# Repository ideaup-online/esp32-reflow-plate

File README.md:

# Solder Reflow Plate Prototype

This is an ESP32 project for controlling a PCB-based solder reflow plate. The solder reflow plate used in this prototype was made using gerbers from [AfterEarthLTD's solder reflow plate](https://github.com/AfterEarthLTD/Solder-Reflow-Plate).

This project was created out of the need to assemble boards using solder reflow. I have some project ideas involving parts that have footprints that can't be soldered any other way.

I became aware of AfterEarthLTD's design after it was featured in a Great Scott! video on YouTube.

At the time I started this, ATmega328 chips are still not available and the code for the ATmega 4809 revision was not yet completed. So, I decided to send the gerbers for the ATmega 4809 revision to JLCPCB to be manufactured.

## Connecting the Solder Reflow Plate to Breadboard Prototype

The boards were populated with only the mosfet (with associated capacitor and zener diode) and the temp sensor (with associated capacitor). I also simply used a 1nF capacitor for both to reduce the number of parts I needed to purchase.

After that, an XT60 connector was soldered with pigtails to the pads for the barrel connector (I did not use the barrel connector). Leads were soldered for the positive side of the XT60, ground, 5V, the gate of the mosfet, and the output of the temp sensor. The positive side of the XT60 was picked up from the pad for the big capacitor that goes next to the barrel connector. Ground and 5V were picked up from the OLED connector through holes. The lead for the gate of the mosfet was soldered directly to the gate pin/pad of the mosfet (mosfet is installed on board). The temp sensor output was picked up from the ATmega 4809 footprint. The leads were terminated in a dupont connector for ease of breadboarding.

I powered all this from the XT60 using battery power of ~13.5V. That voltage was brought over to a breadboard where the rest of the components and the ESP32 were connected. 3.3V from the ESP32 is sent to the board via the 5V lead. This is fine because the only thing I populated that uses the 5V is the temp sensor and it is just as happy with 3.3V. The ground of the board is connected to the ground of the breadboard components. Finally, the gate and temp sensor voltage are passed to the breadboard via their leads.

The battery voltage is brought down to 5V with an XL4015 buck converter to power the ESP32 dev kit board. The ESP32 dev kit then provides 3.3V to everything else.

## Modifications to AfterEarthLTD's Design

Aside from the obvious of using an ESP32 instead of an ATmega, a couple of changes have been made.

The mosfet would not be turned on all the way by simply connecting the gate to one of the ESP32 GPIOs. The max output of 3.3V would not be sufficient. Therefore a DGD0215 gate driver has been used to drive the mosfet.

Also, the ESP32 ADC is not very linear. So, I opted to use a MAX11645 12-bit ADC and MCP1501-20 voltage reference. The LMT85 temp sensor tops out at around 1.9V on its output, so I chose the MCP1501-20 2.048V reference based on that.

Finally, an LED has been added to show when the heater is on (D1).

## 3D Printed Base

A simple 3D printed base has been created. This keeps the board from burning my desk when it gets hot. The STL file for it is here. It needs 4x M3x12 screws, 2x M3 washers, and 4x M3 nuts to assemble. I printed it in PETG on a Prusa Mini.

## Code

The code is not yet complete. The goal is to have the ability to have the board follow a solder reflow profile reasonably closely while being controlled and monitored via a web app running on the ESP32.

For now, there is a 128x64 OLED display just to monitor temperatures. It displays the value from the LMT85 as well as two K-type thermocouples attached via Adafruit MAX31855 breakout boards.

The current version of the code ensures that everything powers up without the heater coming on. The on-board button for GPIO0 can be used to turn on the heater (heater is only on while the button is pressed).

This readme will be updated as the code evolves.

## Should You Build One?

As of now, I would say no. My goal is to spin a new board based on the changes outlined above. I'd also like to try to make the working surface a bit larger than the current 50x70mm.

All that is going to take a little exploring and experimenting. That said, if you would like to do such exploration on your own, then by all means build this as is!

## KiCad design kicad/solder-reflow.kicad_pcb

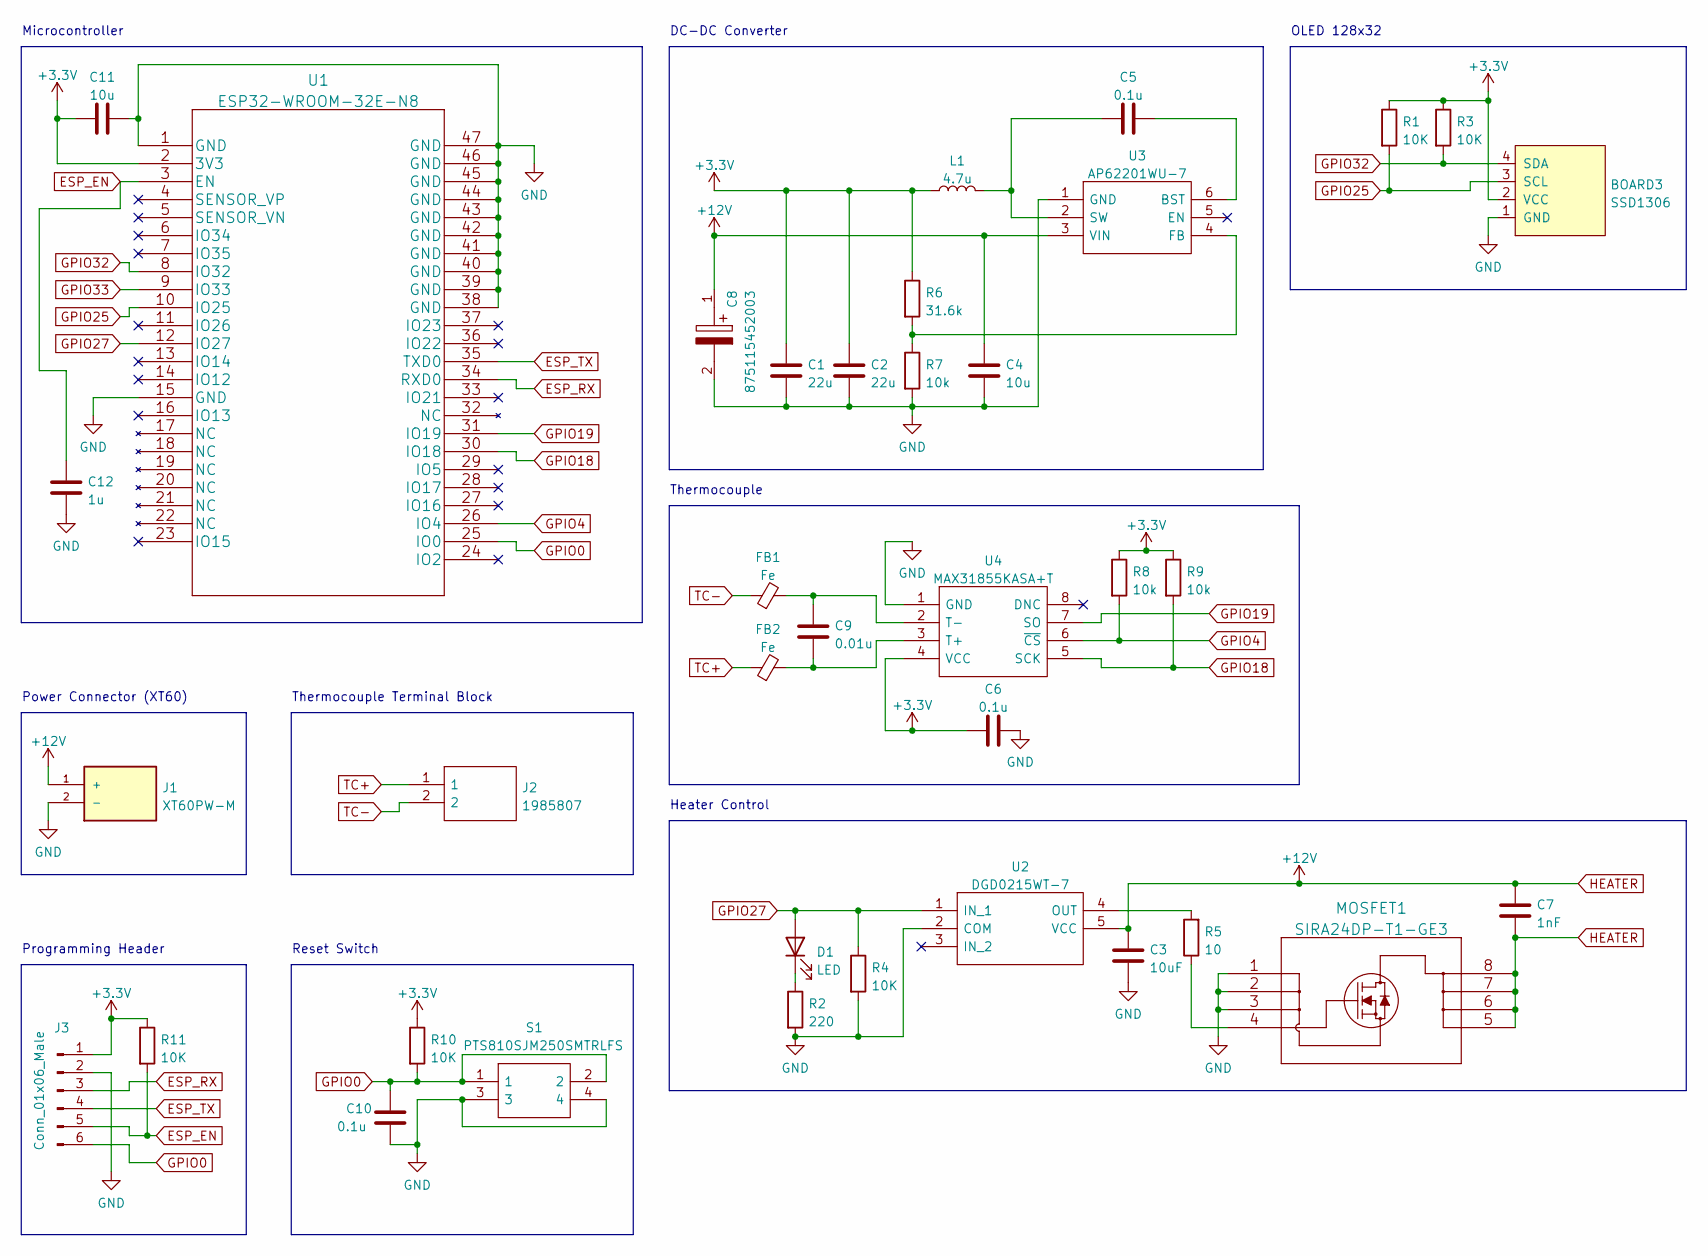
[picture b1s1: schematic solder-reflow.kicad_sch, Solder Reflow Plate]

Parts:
BOARD3: SSD1306; SSD1306-0.91-OLED-4pin-128x32
C1, C2: 22u; 0805
C3: 10uF; 0603
C4: 10u; 0805
C5, C6, C10: 0.1u; 0603
C7: 1nF; 0603
C8: 875115452003; CAPAE830X870N; Mouser Part Number 710-875115452003
C9: 0.01u; 0603
C11: 10u; 0603
C12: 1u; 0603
D1: LED; LED_0603
FB1, FB2: Fe; 0603
J1: XT60PW-M; AMASS_XT60PW-M; PARTREV V1.2
J2: 1985807; Mouser Part Number 651-1985807
J3: Conn_01x06_Male; PinHeader_1x06_P2.54mm_Vertical
L1: 4.7u; IND_NR6028T4R7M
MOSFET1: SIRA24DP-T1-GE3
R1, R3, R4, R10, R11: 10K; 0603
R2: 220; 0603
R5: 10; 0603
R6: 31.6k; 0603
R7, R8, R9: 10k; 0603
S1: PTS810SJM250SMTRLFS; PTS810SJG250SMTRLFS; Mouser Part Number 611-PTS810SJM250SMTR
U1: ESP32-WROOM-32E-N8
U2: DGD0215WT-7; SOT95P280X110-5N; Mouser Part Number 621-DGD0215WT-7
U3: AP62201WU-7; SOT95P280X100-6N; Mouser Part Number 621-AP62201WU-7
U4: MAX31855KASA+T; SOIC127P600X175-8N; Mouser Part Number 700-MAX31855KASA+T

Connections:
+3V3: BOARD3.2 (VCC), C1.1, C2.1, C6.2, C11.1, J3.1, L1.1, R1.1, R3.1, R6.1, R8.1, R9.1, R10.1, R11.1, U1.2 (3V3), U4.4 (VCC)
ESP_EN: C12.2, J3.5, R11.2, U1.3 (EN)
ESP_RX: J3.3, U1.34 (RXD0)
ESP_TX: J3.4, U1.35 (TXD0)
GND: BOARD3.1 (GND), C1.2, C2.2, C3.2, C4.2, C6.1, C8.2, C10.2, C11.2, C12.1, J1.2 (-), J3.2, MOSFET1.1, MOSFET1.2, MOSFET1.3, R2.2, R4.2, R7.2, S1.3, S1.4, U1.1 (GND), U1.15 (GND), U1.38 (GND), U1.39 (GND), U1.40 (GND), U1.41 (GND), U1.42 (GND), U1.43 (GND), U1.44 (GND), U1.45 (GND), U1.46 (GND), U1.47 (GND), U2.2 (COM), U3.1 (GND), U4.1 (GND)
GPIO0: C10.1, J3.6, R10.2, S1.1, S1.2, U1.25 (IO0)
GPIO4: R8.2, U1.26 (IO4), U4.6 (~CS)
GPIO18: R9.2, U1.30 (IO18), U4.5 (SCK)
GPIO19: U1.31 (IO19), U4.7 (SO)
GPIO25: BOARD3.3 (SCL), R1.2, U1.10 (IO25)
GPIO27: D1.2 (A), R4.1, U1.12 (IO27), U2.1 (IN_1)
GPIO32: BOARD3.4 (SDA), R3.2, U1.8 (IO32)
GPIO33: U1.9 (IO33)
HEATER: C3.1, C4.1, C7.1, C7.2, C8.1, J1.1 (+), MOSFET1.5, MOSFET1.6, MOSFET1.7, MOSFET1.8, U2.5 (VCC), U3.3 (VIN)
unnamed: C5.1, L1.2, U3.2 (SW)
unnamed: C5.2, U3.6 (BST)
unnamed: C9.1, FB1.2, U4.2 (T-)
unnamed: C9.2, FB2.2, U4.3 (T+)
unnamed: D1.1 (K), R2.1
unnamed: MOSFET1.4, R5.1
unnamed: R5.2, U2.4 (OUT)
unnamed: R6.2, R7.1, U3.4 (FB)
TC+: FB2.1, J2.1
TC-: FB1.1, J2.2

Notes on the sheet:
DC-DC Converter
Thermocouple
Heater Control
Reset Switch
Thermocouple Terminal Block
Microcontroller
Power Connector (XT60)
OLED 128x32
Programming Header

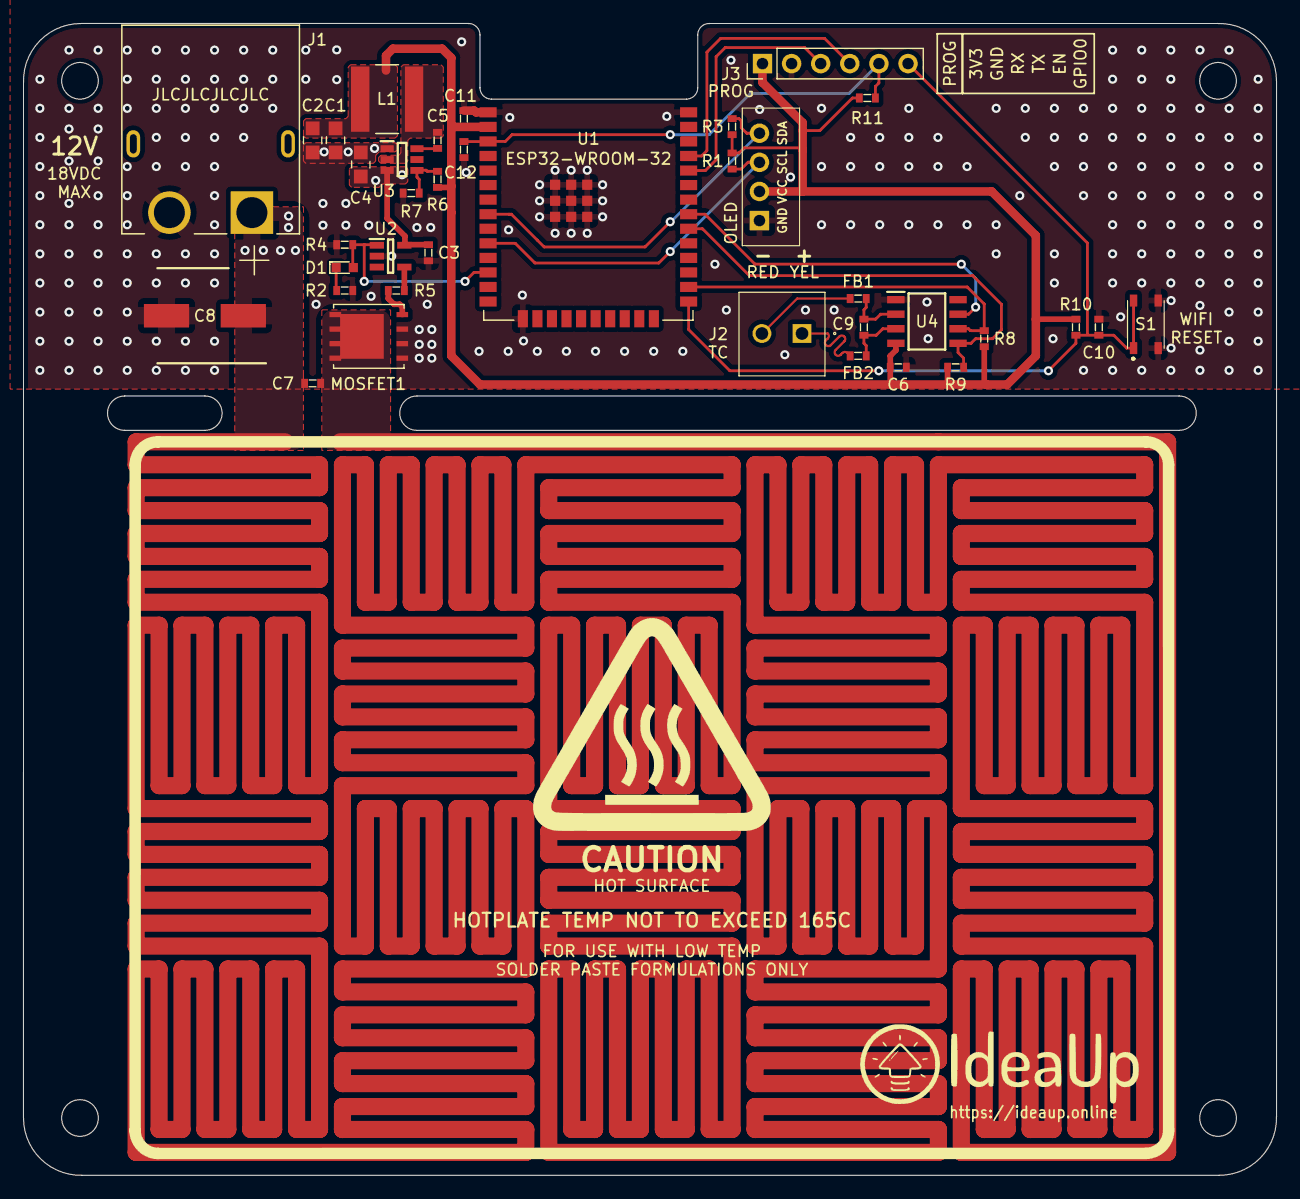
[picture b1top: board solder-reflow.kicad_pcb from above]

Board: 2 copper layers, 109.3 x 100.5 mm, 37 parts (0 on the bottom side), 23 nets.

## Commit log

2022-11-25 Fixed typo in schematic
2022-11-28 Added PID controller; did initial tune
2022-12-01 Added tcp server to serve csv data; found good PID values; started changes to follow reflow curve
2022-12-01 Added code to make setpoint follow reflow curve
2022-12-01 Tweaked PID values
2022-12-21 Added KiCad project for esp32-based PCB
2022-12-22 Tweaked layout; refined buck layout; added graphics
2022-12-22 Missed one file; refined gitignore
2022-12-22 Changed tactile switch part

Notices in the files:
parts and their libraries:
Copyright 2021 Accelerated Designs. All rights reserved.
